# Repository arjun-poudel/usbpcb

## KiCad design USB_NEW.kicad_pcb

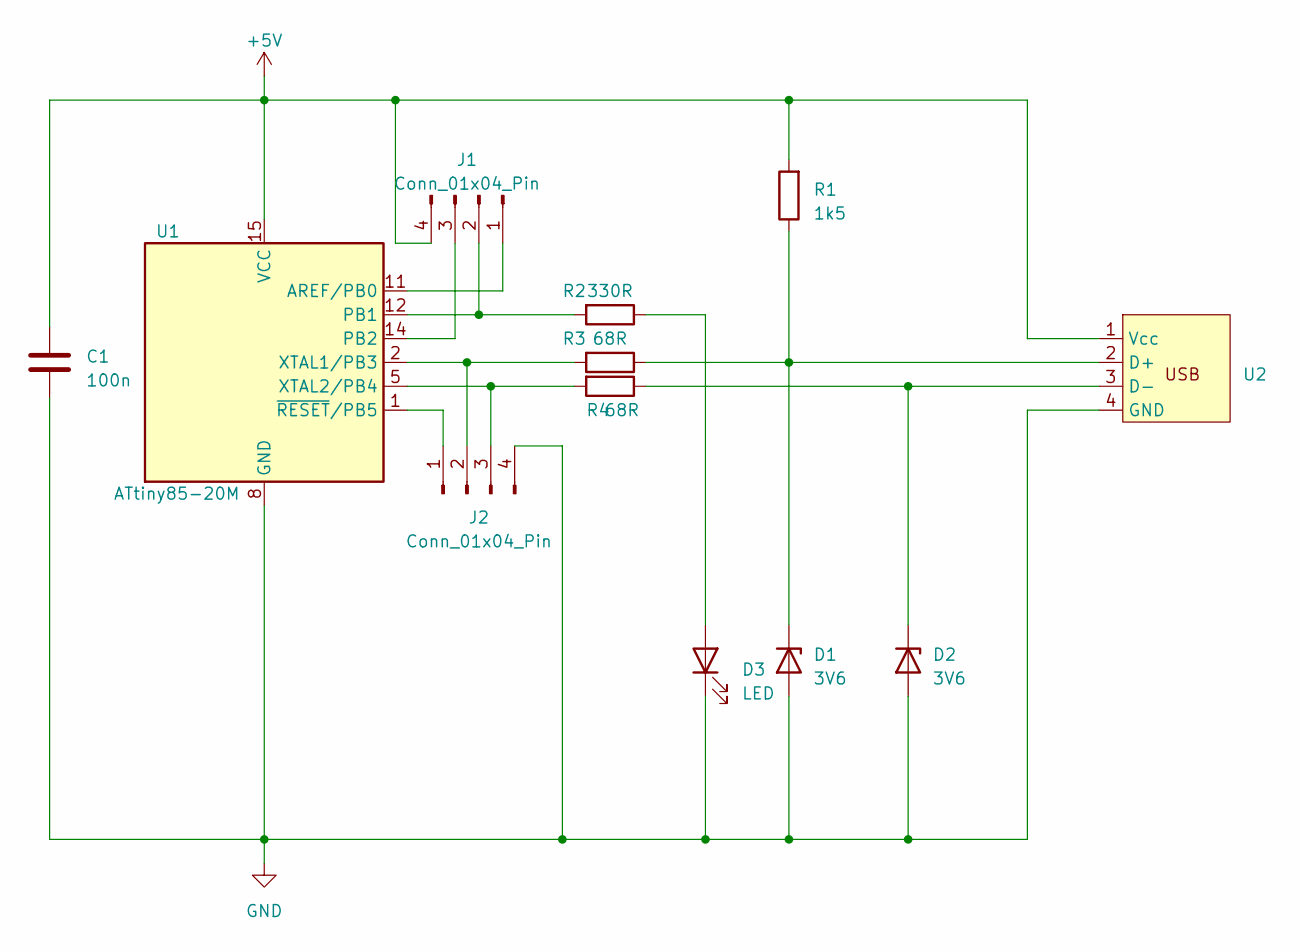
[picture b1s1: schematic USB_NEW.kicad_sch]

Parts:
C1: 100n; C_1206_3216Metric_Pad1.33x1.80mm_HandSolder
D1, D2: 3V6; D_SOD-123
D3: LED; LED_0603_1608Metric_Pad1.05x0.95mm_HandSolder
J1, J2: Conn_01x04_Pin; FanPinHeader_1x04_P2.54mm_Vertical
R1: 1k5; R_0805_2012Metric_Pad1.20x1.40mm_HandSolder
R2: 330R; R_0805_2012Metric_Pad1.20x1.40mm_HandSolder
R3, R4: 68R; R_0805_2012Metric_Pad1.20x1.40mm_HandSolder
U1: ATtiny85-20M; QFN-20-1EP_4x4mm_P0.5mm_EP2.6x2.6mm
U2: USB_PCB_Connector

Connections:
+5V: C1.1, J1.4, R1.2, U1.15 (VCC), U2.1 (Vcc)
GND: C1.2, D1.2 (A), D2.2 (A), D3.1 (K), J2.4, U1.8 (GND), U1.21 (GND), U2.4 (GND)
unnamed: D1.1 (K), R1.1, R3.1, U2.2 (D+)
unnamed: D2.1 (K), R4.1, U2.3 (D-)
unnamed: D3.2 (A), R2.1
unnamed: J1.1, U1.11 (AREF/PB0)
unnamed: J1.2, R2.2, U1.12 (PB1)
unnamed: J1.3, U1.14 (PB2)
unnamed: J2.1, U1.1 (~RESET/PB5)
unnamed: J2.2, R3.2, U1.2 (XTAL1/PB3)
unnamed: J2.3, R4.2, U1.5 (XTAL2/PB4)

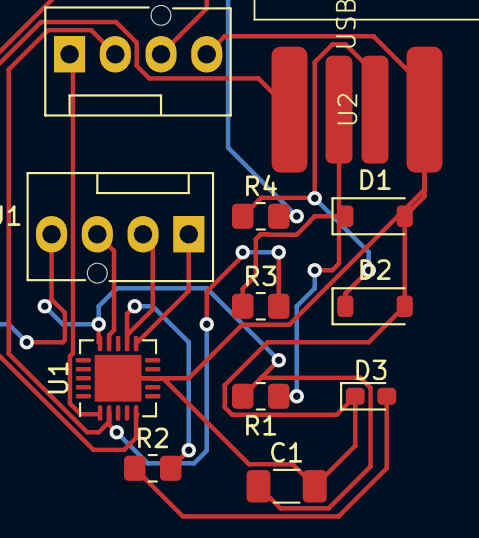
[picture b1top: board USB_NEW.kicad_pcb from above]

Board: 2 copper layers, 12 parts (0 on the bottom side), 11 nets.

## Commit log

2024-10-09 Add files via upload
    Trying to be better candidates for embedded jobs
